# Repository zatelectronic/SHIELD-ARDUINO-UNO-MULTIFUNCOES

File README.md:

# SHIELD-ARDUINO-UNO-MULTIFUNCOES

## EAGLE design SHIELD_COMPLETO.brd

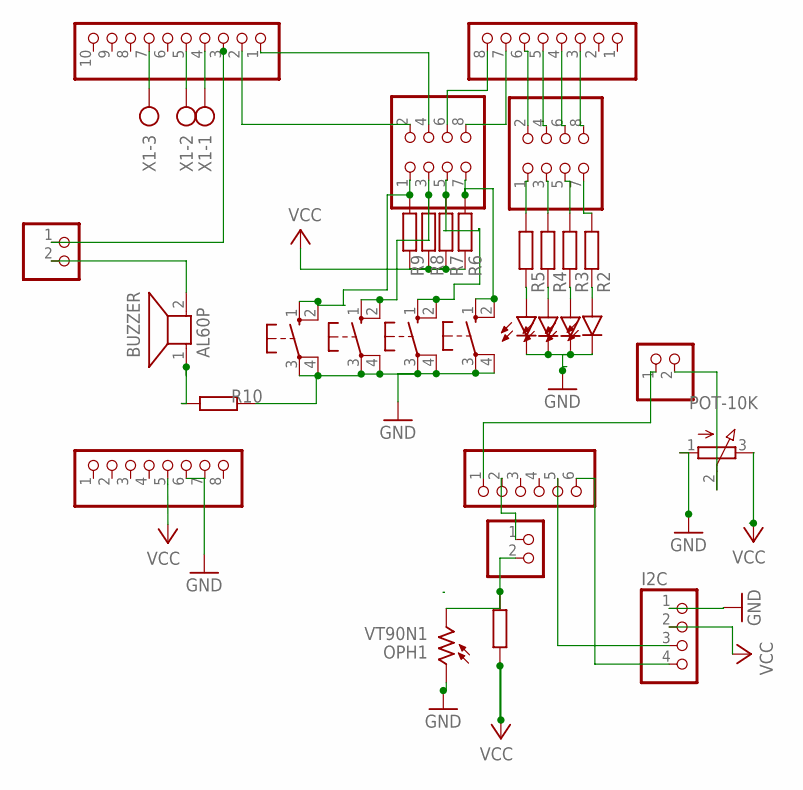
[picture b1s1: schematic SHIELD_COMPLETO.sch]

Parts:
AD: 6x1F-H8.5; 1X06
BOT1, BOT2, BOT3, BOT4: 10-XX; B3F-10XX
BUZZER: AL60P
I2C: PINHD-1X4; 1X04
IOH: 10x1F-H8.5; 1X10
IOL: 8x1F-H8.5; 1X08
J10: PINHD-1X2; 1X02
JP1, JP2: PINHD-2X4; 2X04
JP3, JP4: PINHD-1X2; 1X02
LED1, LED2, LED3, LED4: LED5MM
OPH1: VT90N1; VT900
POT-10K: 3RP/1610N
POWER: 8x1F-H8.5; 1X08
R1, R2, R3, R4, R5, R6, R7, R8, R9, R10: R-EU_0204/7; 0204/7
X1: AK300/3

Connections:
GND: BOT1.3, BOT1.4 (P1), BOT2.3, BOT2.4 (P1), BOT3.3, BOT3.4 (P1), BOT4.3, BOT4.4 (P1), I2C.1, LED1.K (C), LED2.K (C), LED3.K (C), LED4.K (C), OPH1.1, POT-10K.1 (A), POWER.6, POWER.7, R10.1
unnamed: JP1.1, R5.2
unnamed: IOL.3, JP1.8
unnamed: IOL.4, JP1.6
unnamed: IOL.5, JP1.4
unnamed: IOL.6, JP1.2
unnamed: JP1.3, R4.2
unnamed: JP1.5, R3.2
unnamed: JP1.7, R2.2
unnamed: LED1.A, R2.1
unnamed: LED2.A, R3.1
unnamed: LED3.A, R4.1
unnamed: LED4.A, R5.1
unnamed: IOL.7, JP2.8
unnamed: IOL.8, JP2.6
unnamed: IOH.1, JP2.4
unnamed: IOH.2, JP2.2
unnamed: JP4.2, POT-10K.2 (S)
unnamed: BOT1.1 (S), BOT1.2 (S1), JP2.7, R6.2
unnamed: JP3.2, OPH1.2, R1.1
unnamed: AD.2, JP3.1
unnamed: BOT4.1 (S), BOT4.2 (S1), JP2.1, R9.2
unnamed: BOT3.1 (S), BOT3.2 (S1), JP2.3, R8.2
unnamed: BOT2.1 (S), BOT2.2 (S1), JP2.5, R7.2
unnamed: BUZZER.1, R10.2
unnamed: IOH.7, X1.3
unnamed: IOH.3, J10.1
unnamed: IOH.5, X1.2
unnamed: AD.5, I2C.3
unnamed: AD.6, I2C.4
unnamed: AD.1, JP4.1
unnamed: IOH.4, X1.1
unnamed: BUZZER.2, J10.2
VCC: I2C.2, POT-10K.3 (E), POWER.5, R1.2, R6.1, R7.1, R8.1, R9.1

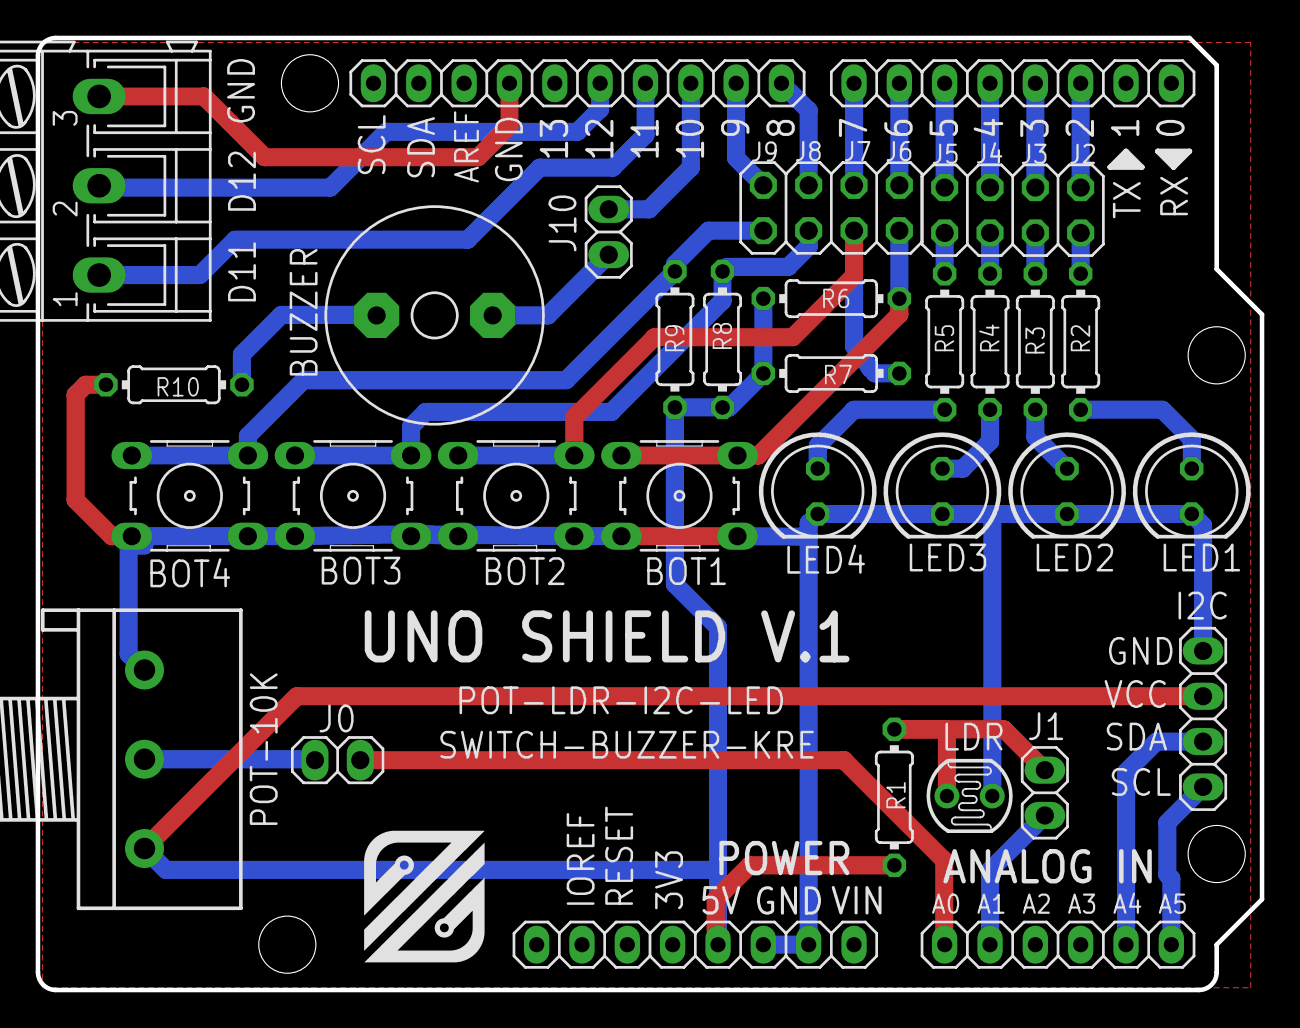
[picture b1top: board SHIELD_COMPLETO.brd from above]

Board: 2 copper layers, 68.6 x 53.3 mm, 33 parts (0 on the bottom side), 34 nets.

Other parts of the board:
U$1: SIMBOLO_MEDIO

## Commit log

2021-10-24 PRIMEIRO ENVIO
2021-10-25 ATUALIZAÇÃO
2021-11-27 ENVIO 2
2021-11-27 ENVIO 3
